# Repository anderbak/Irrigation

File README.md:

# Irrigation

ESPHome 16 Channel Irrigation Controller designed with KiCad v5

https://selfhostedhome.com/diy-wifi-sprinkler-controller-using-esp8266-part-1/

https://www.instructables.com/IO-Expander-for-ESP32-ESP8266-and-Arduino/

https://esphome.io/components/sprinkler.html

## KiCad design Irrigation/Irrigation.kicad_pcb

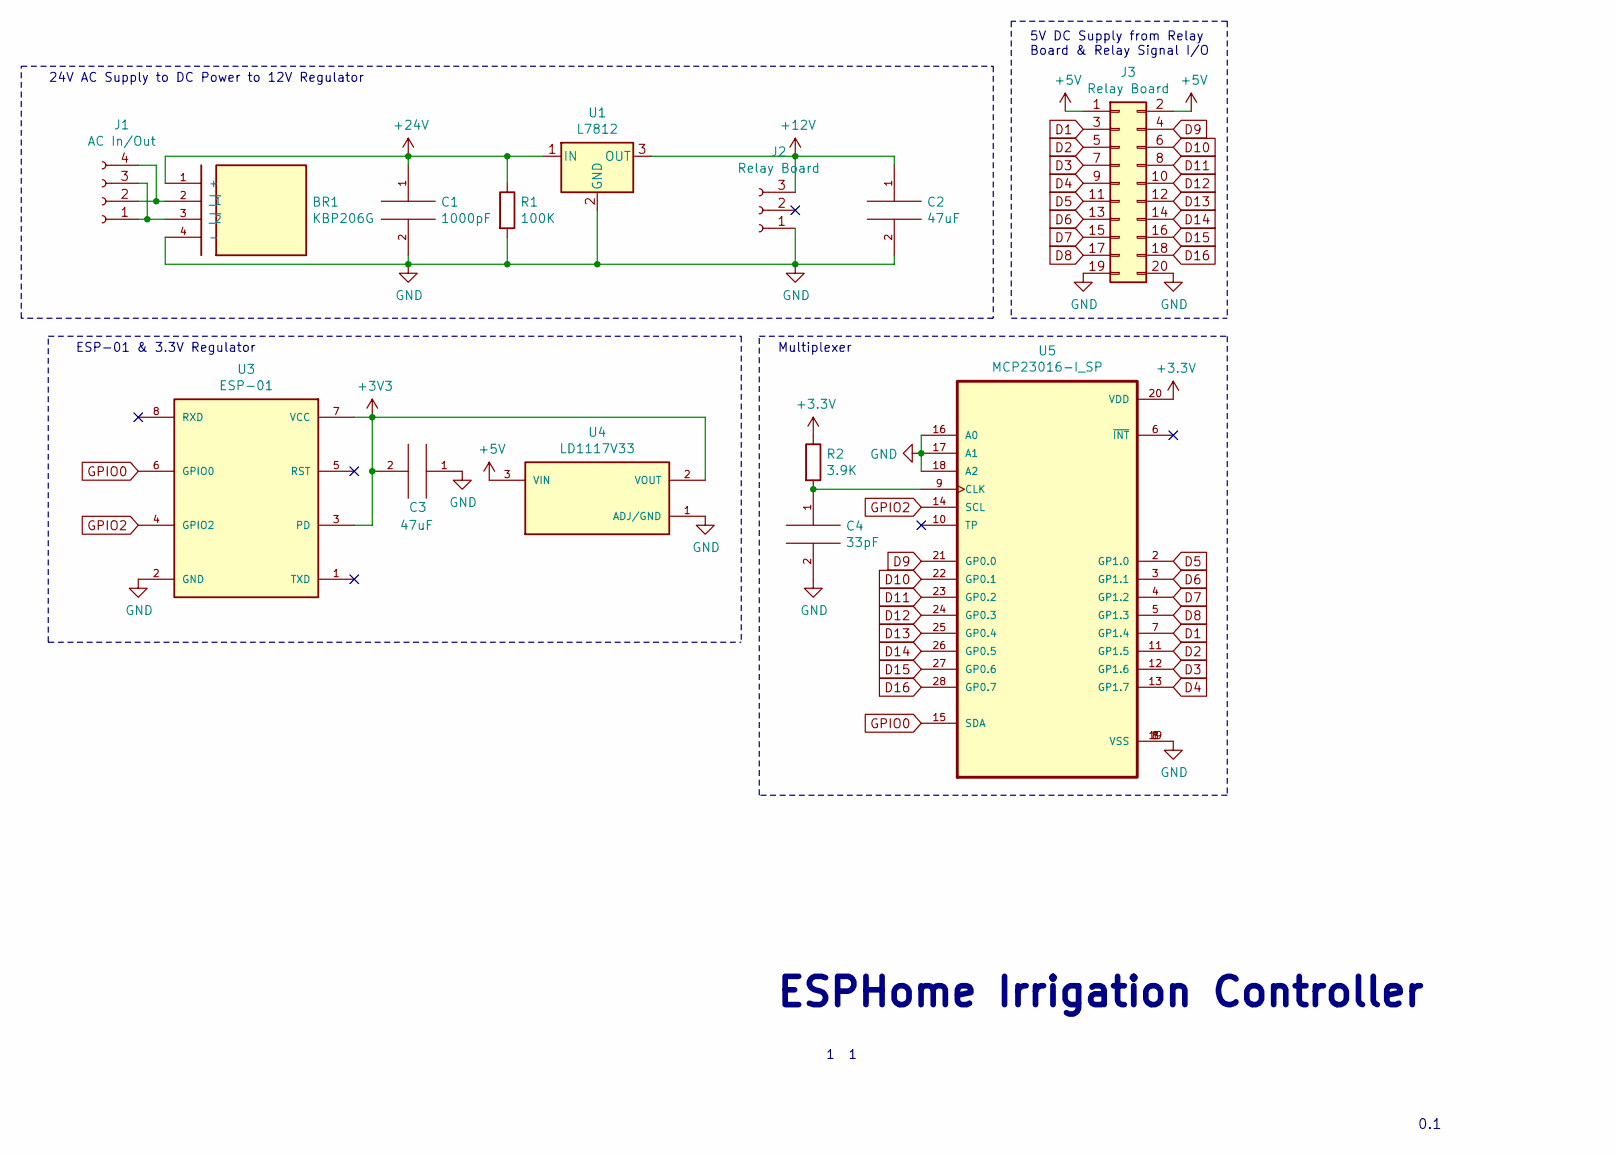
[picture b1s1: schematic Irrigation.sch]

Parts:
BR1: KBP206G; Mouser_Part_Number 621-KBP206G
C1: 1000pF; C_Disc_D3.8mm_W2.6mm_P2.50mm
C2, C3: 47uF; CAP_RDEC71E476MWK1H03B
C4: 33pF; C_Rect_L4.0mm_W2.5mm_P2.50mm
J1: AC In/Out; TerminalBlock_Phoenix_MPT-0,5-4-2.54_1x04_P2.54mm_Horizontal
J2: Relay Board; PinHeader_1x03_P2.54mm_Vertical
J3: Relay Board; SULLINS_PPPC102LFBN-RC
R1: 100K; R_Axial_DIN0207_L6.3mm_D2.5mm_P7.62mm_Horizontal
R2: 3.9K; R_Axial_DIN0207_L6.3mm_D2.5mm_P7.62mm_Horizontal
U1: L7812; TO255P1040X460X1968-3
U3: ESP-01; PinHeader_2x04_P2.54mm_Vertical
U4: LD1117V33; TO255P1020X450X1968-3; PARTREV 37
U5: MCP23016-I_SP; DIP787W46P254L3467H508Q28

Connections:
+5V: J3.1, J3.2, U4.3 (VIN)
+24V: BR1.1 (+), C1.1, R1.1, U1.1 (IN)
D1: J3.3, U5.7 (GP1.4)
D2: J3.5, U5.11 (GP1.5)
D3: J3.7, U5.12 (GP1.6)
D4: J3.9, U5.13 (GP1.7)
D5: J3.11, U5.2 (GP1.0)
D6: J3.13, U5.3 (GP1.1)
D7: J3.15, U5.4 (GP1.2)
D8: J3.17, U5.5 (GP1.3)
D9: J3.4, U5.21 (GP0.0)
D10: J3.6, U5.22 (GP0.1)
D11: J3.8, U5.23 (GP0.2)
D12: J3.10, U5.24 (GP0.3)
D13: J3.12, U5.25 (GP0.4)
D14: J3.14, U5.26 (GP0.5)
D15: J3.16, U5.27 (GP0.6)
D16: J3.18, U5.28 (GP0.7)
GND: BR1.4 (-), C1.2, C2.2, C3.1, C4.2, J2.1, J3.19, J3.20, R1.2, U1.2 (GND), U3.2 (GND), U4.1 (ADJ/GND), U5.1 (VSS), U5.8 (VSS), U5.16 (A0), U5.17 (A1), U5.18 (A2), U5.19 (VSS)
GPIO0: U3.6 (GPIO0), U5.15 (SDA)
GPIO2: U3.4 (GPIO2), U5.14 (SCL)
unnamed: BR1.2 (~_1), J1.2, J1.4
unnamed: BR1.3 (~_2), J1.1, J1.3
unnamed: C2.1, J2.3, U1.3 (OUT)
unnamed: C4.1, R2.2, U5.9 (CLK)

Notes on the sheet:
24V AC Supply to DC Power to 12V Regulator
ESP-01 & 3.3V Regulator
Multiplexer
5V DC Supply from Relay Board & Relay Signal I/O
ESPHome Irrigation Controller
1 1
0.1

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
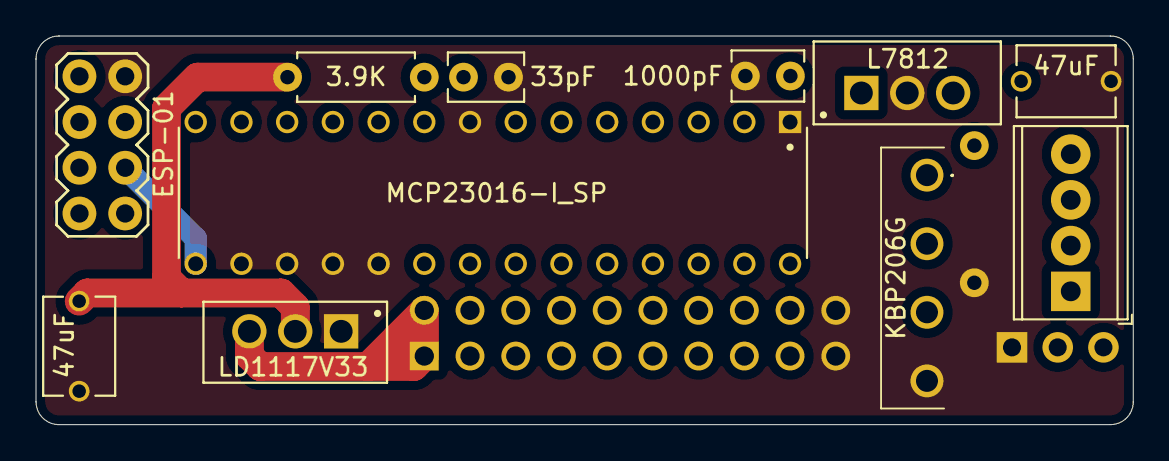
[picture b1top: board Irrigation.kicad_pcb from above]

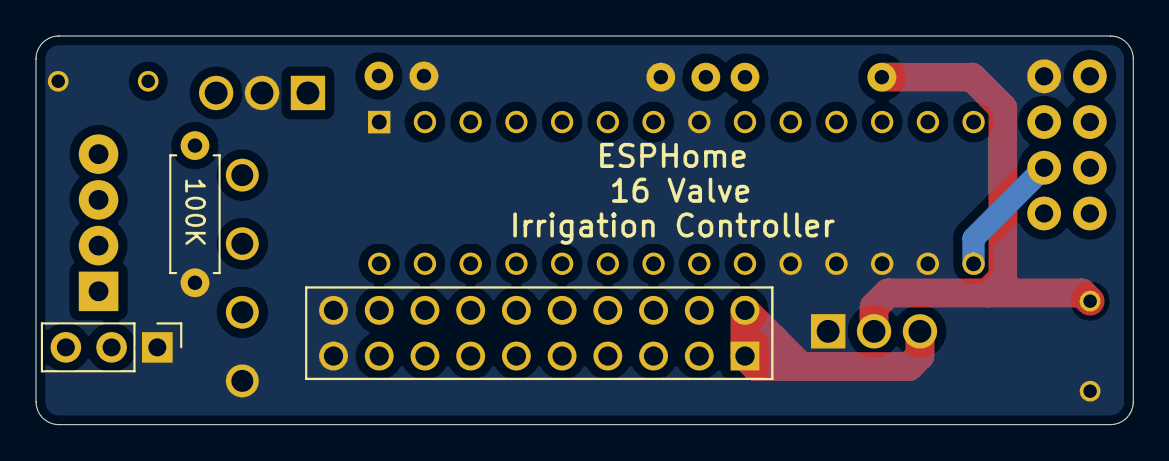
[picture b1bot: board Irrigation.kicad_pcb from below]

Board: 4 copper layers, 61.0 x 21.6 mm, 14 parts (3 on the bottom side), 26 nets.
